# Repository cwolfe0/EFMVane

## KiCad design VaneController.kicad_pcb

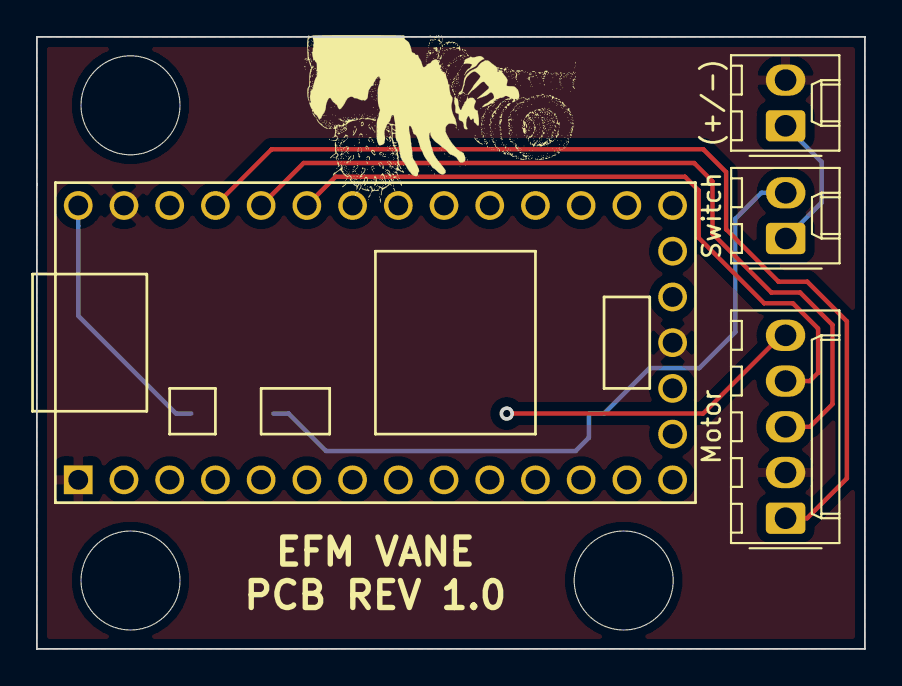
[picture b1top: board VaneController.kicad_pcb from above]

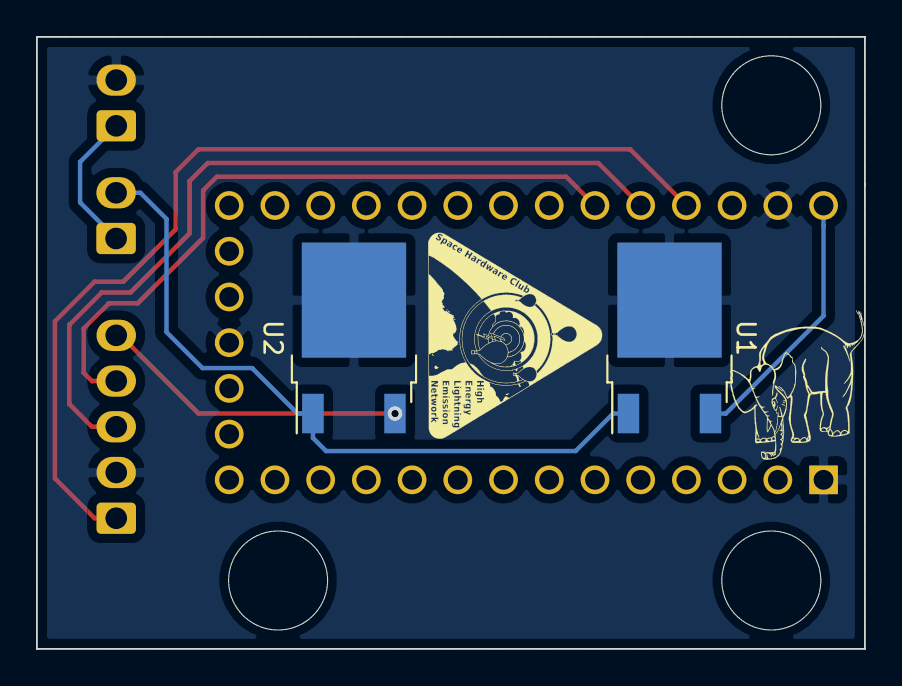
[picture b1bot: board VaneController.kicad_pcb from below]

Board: 2 copper layers, 46.0 x 34.0 mm, 6 parts (2 on the bottom side), 8 nets.

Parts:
(+/-): Conn_01x02; Molex_KK-254_AE-6410-02A_1x02_P2.54mm_Vertical
Motor: Conn_01x05; Molex_KK-254_AE-6410-05A_1x05_P2.54mm_Vertical
Switch: Conn_01x02_Male; Molex_KK-254_AE-6410-02A_1x02_P2.54mm_Vertical
U1: MC78M05; TO-252-2
U2: MC78M12; TO-252-2
U3: Teensy3.2; Teensy30_31_32_LC

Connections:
/1: Motor.1, U3.30
/2: Motor.3, U3.29
/3: Motor.4, U3.28
/5V: U1.3, U3.33
/12V: Motor.5, U2.3
/BATT: Switch.2, U1.1, U2.1
/SWITCH: (+/-).1, Switch.1
GND: (+/-).2, Motor.2, U1.2, U2.2, U3.1, U3.17, U3.32

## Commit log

2019-06-05 Add files
